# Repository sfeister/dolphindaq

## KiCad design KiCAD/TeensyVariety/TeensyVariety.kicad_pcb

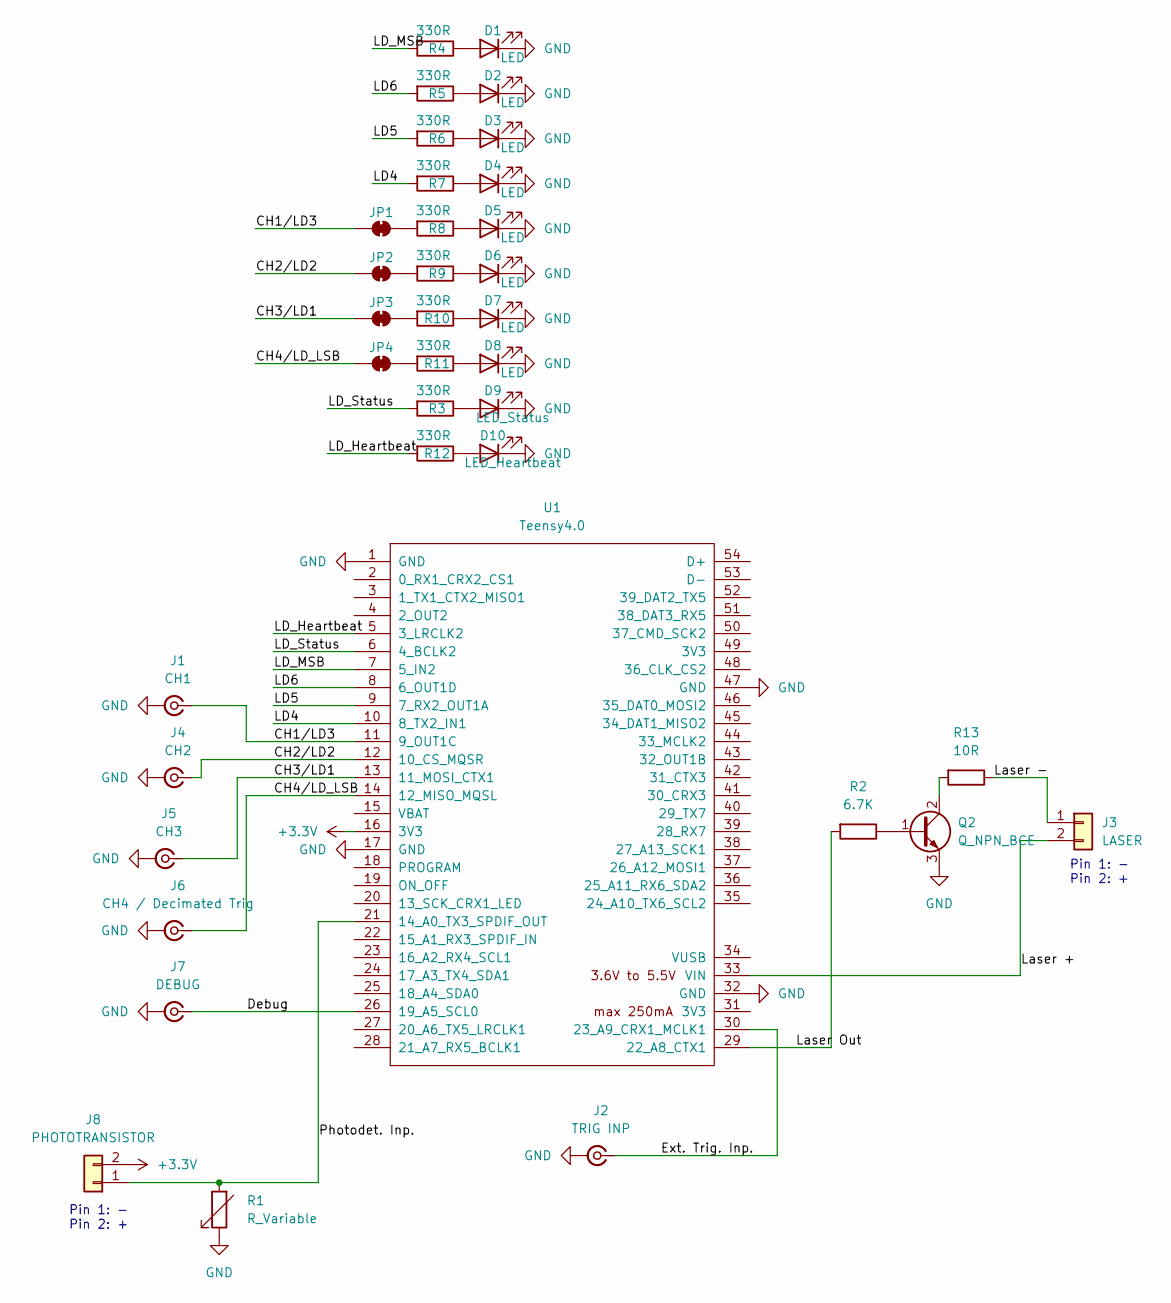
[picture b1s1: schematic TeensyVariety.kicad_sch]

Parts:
D1, D2, D3, D4, D5, D6, D7, D8: LED; LED_0805_2012Metric
D9: LED_Status; LED_0805_2012Metric
D10: LED_Heartbeat; LED_0805_2012Metric
J1: CH1; SMA_Amphenol_132134_Vertical
J2: TRIG INP; SMA_Amphenol_132134_Vertical
J3: LASER; JST_EH_S2B-EH_1x02_P2.50mm_Horizontal
J4: CH2; SMA_Amphenol_132134_Vertical
J5: CH3; SMA_Amphenol_132134_Vertical
J6: CH4 / Decimated Trig; SMA_Amphenol_132134_Vertical
J7: DEBUG; SMA_Amphenol_132134_Vertical
J8: PHOTOTRANSISTOR; JST_EH_S2B-EH_1x02_P2.50mm_Horizontal
JP1, JP2, JP3, JP4: Isolator; SolderJumper-2_P1.3mm_Bridged2Bar_Pad1.0x1.5mm
Q2: Q_NPN_BCE; SOT-23
R1: R_Variable; R_0805_2012Metric
R2: 6.7K; R_0805_2012Metric
R3, R4, R5, R6, R7, R8, R9, R10, R11, R12: 330R; R_0805_2012Metric
R13: 10R; R_0805_2012Metric
U1: Teensy4.0; Teensy40

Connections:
+3.3V: J8.2, U1.16 (3V3)
/CH1/LD3: J1.1 (In), JP1.1 (A), U1.11 (9_OUT1C)
/CH2/LD2: J4.1 (In), JP2.1 (A), U1.12 (10_CS_MQSR)
/CH3/LD1: J5.1 (In), JP3.1 (A), U1.13 (11_MOSI_CTX1)
/CH4/LD_LSB: J6.1 (In), JP4.1 (A), U1.14 (12_MISO_MQSL)
/Debug: J7.1 (In), U1.26 (19_A5_SCL0)
/Ext. Trig. Inp.: J2.1 (In), U1.30 (23_A9_CRX1_MCLK1)
/LD4: R7.2, U1.10 (8_TX2_IN1)
/LD5: R6.2, U1.9 (7_RX2_OUT1A)
/LD6: R5.2, U1.8 (6_OUT1D)
/LD_Heartbeat: R12.2, U1.5 (3_LRCLK2)
/LD_MSB: R4.2, U1.7 (5_IN2)
/LD_Status: R3.2, U1.6 (4_BCLK2)
/Laser +: J3.2, U1.33 (VIN)
/Laser -: J3.1, R13.1
/Laser Out: R2.2, U1.29 (22_A8_CTX1)
/Photodet. Inp.: J8.1, R1.2, U1.21 (14_A0_TX3_SPDIF_OUT)
GND: D1.1 (K), D2.1 (K), D3.1 (K), D4.1 (K), D5.1 (K), D6.1 (K), D7.1 (K), D8.1 (K), D9.1 (K), D10.1 (K), J1.2 (Ext), J2.2 (Ext), J4.2 (Ext), J5.2 (Ext), J6.2 (Ext), J7.2 (Ext), Q2.3 (E), R1.1, U1.1 (GND), U1.17 (GND), U1.32 (GND), U1.47 (GND)
unnamed: D1.2 (A), R4.1
unnamed: D2.2 (A), R5.1
unnamed: D3.2 (A), R6.1
unnamed: D4.2 (A), R7.1
unnamed: D5.2 (A), R8.1
unnamed: D6.2 (A), R9.1
unnamed: D7.2 (A), R10.1
unnamed: D8.2 (A), R11.1
unnamed: D9.2 (A), R3.1
unnamed: D10.2 (A), R12.1
unnamed: JP1.2 (B), R8.2
unnamed: JP2.2 (B), R9.2
unnamed: JP3.2 (B), R10.2
unnamed: JP4.2 (B), R11.2
unnamed: Q2.1 (B), R2.1
unnamed: Q2.2 (C), R13.2

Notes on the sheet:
Pin 1: - Pin 2: +

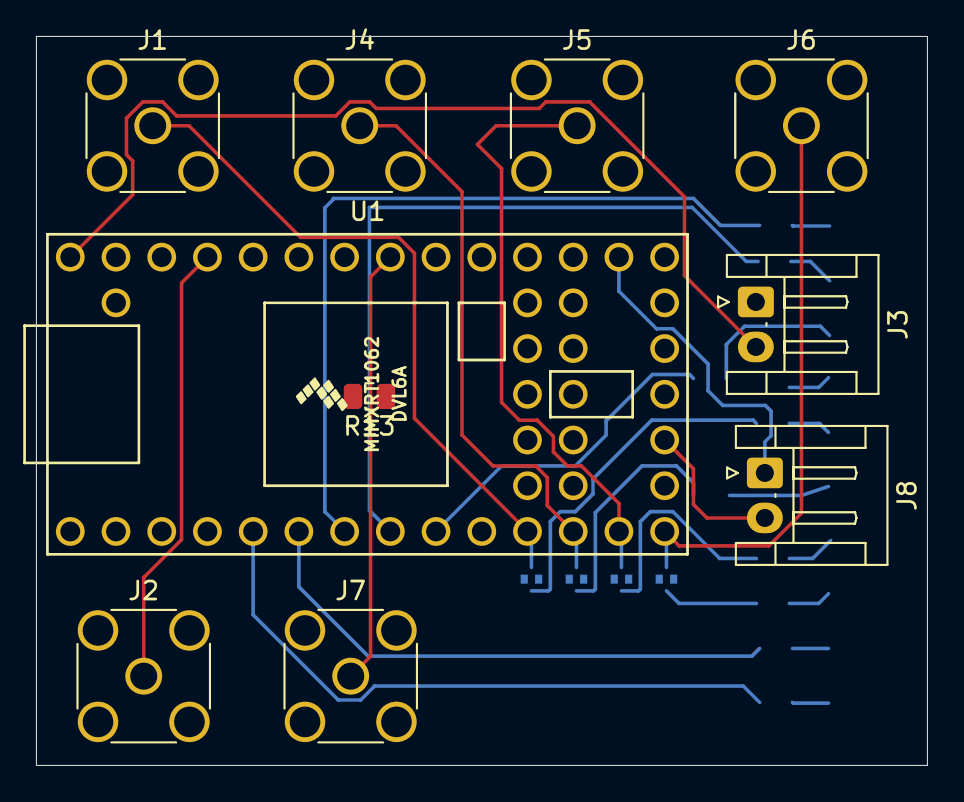
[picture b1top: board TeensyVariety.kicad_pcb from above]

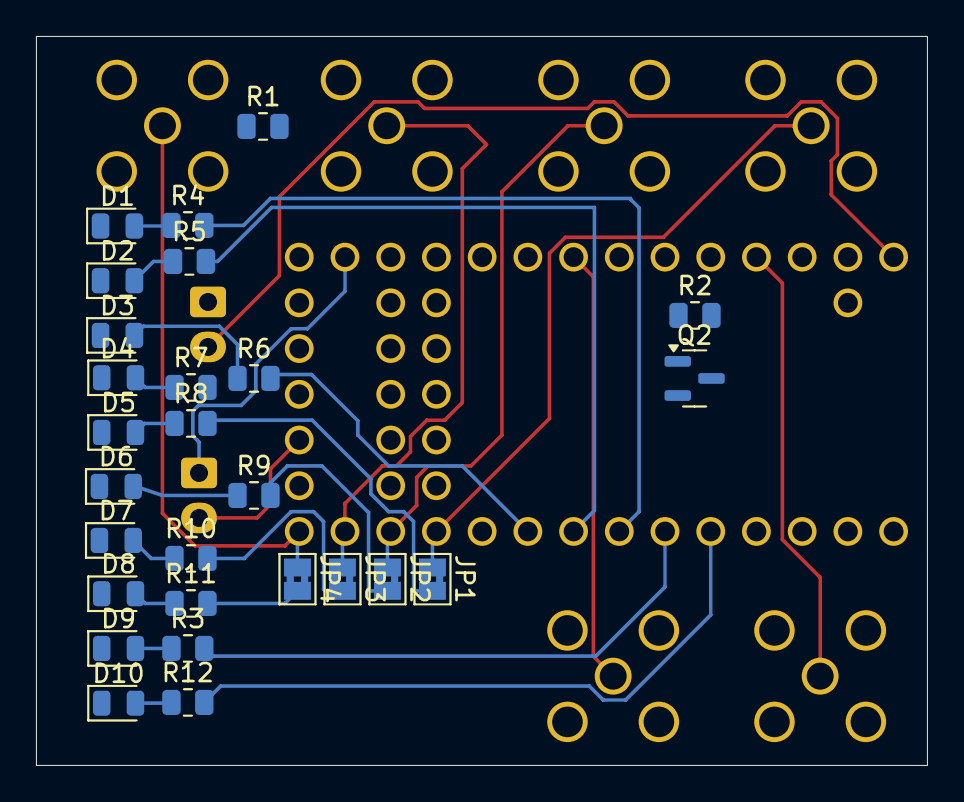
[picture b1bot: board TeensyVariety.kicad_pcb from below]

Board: 2 copper layers, 49.5 x 40.5 mm, 37 parts (27 on the bottom side), 34 nets.

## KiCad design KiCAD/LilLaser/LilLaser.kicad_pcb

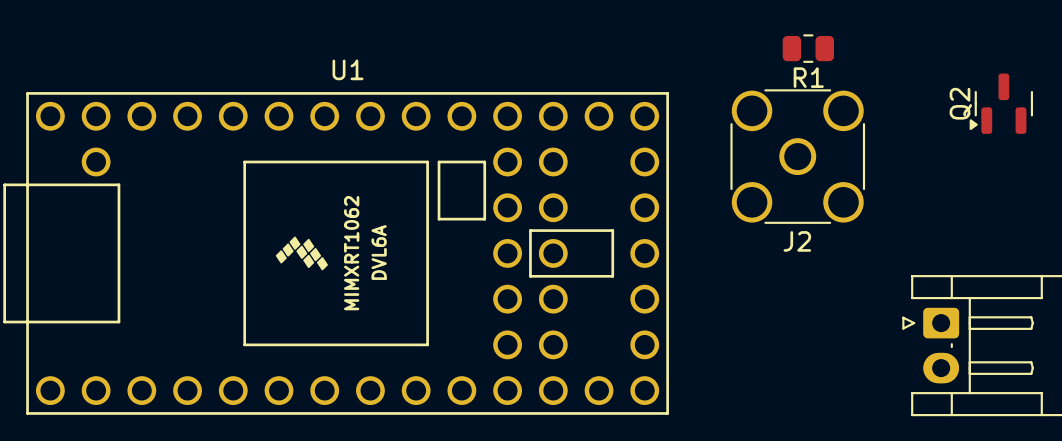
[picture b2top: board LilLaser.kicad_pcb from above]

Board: 2 copper layers, 5 parts (0 on the bottom side), 6 nets, no tracks yet.

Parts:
J2: Conn_Coaxial_Small; SMA_Amphenol_132134_Vertical
J3: Conn_01x02; JST_EH_S2B-EH_1x02_P2.50mm_Horizontal
Q2: Q_NPN_BCE; SOT-23
R1: R; R_0805_2012Metric
U1: Teensy4.0; Teensy40

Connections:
/Ext Trig Inp: J2.1 (In), U1.23 (16_A2_RX4_SCL1)
/Laser +: J3.2, U1.33 (VIN)
/Laser -: J3.1, Q2.2 (C)
/Laser Out: R1.2, U1.22 (15_A1_RX3_SPDIF_IN)
GND: J2.2 (Ext), Q2.3 (E), U1.1 (GND), U1.17 (GND), U1.32 (GND)
unnamed: Q2.1 (B), R1.1

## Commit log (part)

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2021-01-23 Adding Protobuffer templates
2021-01-23 Updated protobuffers
2021-01-23 Updated protobuf folders
2021-01-27 Working on diode_h5 to store the diode type to HDF5 files
2021-01-28 test7-data-server.py and test7-diode1-client.py are working great together! Now just need to have the server keep on looking for connections, and have the clients handle a failure of the server
2021-02-08 Continuing work on data-server; switching over to work on protobuf-c code for Matsunet
2022-06-08 Old update to makefile, not inspected
2022-06-08 Added simple.proto example as directly copied from NanoPB examples folder
2022-06-09 Including NanoPB header files and source code files for convenience
2022-06-09 Added scoping to the diode protobuffer specification, such that Data and Trace don't conflict with other scopes
2022-06-09 New clients in Python to match up with the Nucleo codes
2022-06-09 net10 client now receives hello, settings, and a single trace
2022-06-10 Net10 breaks on the microcontroller side after sending 100 to 500 commits.
2022-06-20 Client for the ADC network test, net12
2022-06-23 Updated terminology of the traces and settings for the photodiode signal
2022-07-01 Net14 client is working well; ready for a test on ADC data
2022-07-06 Added various additional low-level settings from the H7 firmware
2022-07-06 Fixed bug with seconds being represented as uint32 instead of double
2022-07-06 Upgraded from proto2 to proto3 syntax to include the Well-known 'Timestamp' type from Google, so that I can timestamp shots
2022-07-06 Reverted to proto2 because it includes a 'has_' syntax for singletons that I find useful in distinguishing between values of zero, and default values'
2022-07-06 Including protobuf source code for Timestamp well known type
2022-07-11 Updated protobuf for diode to indicate higher level dt - at the ADC conversion level, rather than just the returned trace
2022-07-11 Removed dt_secs option from protobuf for consistency, just using dt and inferred seconds
2022-07-12 Updated name of shot_time from the plural version, to be more consistent
2022-07-12 Continuing to add optional metrics fields
2022-07-13 Added metrics batch size to settings
2022-07-13 Fixed metrics batch size to be an integer
2022-07-14 Added LabVIEW SCPI-style drivers for the Diode H7 20220713 firmware
2022-07-14 Added a new Python folder to hold scripts such as those for data recording onto the Beaglebone
2022-07-15 Added SCPI set/get of trace decimation to the LabVIEW SCPI-like driver
2022-07-15 Test8 server demonstrated 60k acquisition batches for several minutes saved to HDF5, capturing vast majority of shots metrics
2022-07-15 Minor adjustments to gitignores
2022-07-18 Adding optional, simpler arrays for timestamps within metrics
2022-07-19 Added an alternate, precision timing source in the metrics
2022-07-19 Updated naming of the alternative precision timer
2022-07-19 Added a LabVIEW example of visualizing result from HDF5
2022-07-20 LabVIEW portion of this commit goes along with Nucleo Diode H7 20220719 firmware
2022-07-20 Updating linecam protocol file as I develop Hamamatsu line camera H7 firmware
2022-07-23 Displays for the Hamaline camera
2022-07-24 Adding a new device: Rosie
2022-07-29 Updated all code to match Nucleo firmware 20220728 - note addition of metadata to the diode-recorder
2022-08-01 Updating VIs to call common subroutines
2022-08-03 Updated linecam proto file to include the T1 delay time
2022-08-03 Updating diode controls
2022-09-01 Updating lab launcher and tested; it basically works - Rosie and Diode control panels are now ready to go back into real testing in a lab setting, including saving to local file
2023-01-18 Lingering change to LabVIEW aliases from months ago
2023-02-15 Updated Rosie SCPI keywords to match Nucleo Rosie 20230215 firmware
2023-02-27 Beginning EPICS driver for Rosie firmware; confirmed that this first simplest StreamDevice startup script works for getting SCPI identification
2023-02-27 Adding Rosie into EPICS works well; created example Python code of how to translate between global trigger count and local trigger count for a rosie device
2023-03-03 Created a new device, BlinkSync, which helps with camera synchronization by providing a visual display of a trigger count
2023-04-04 Updating Serial BlinkSync to work with a frequency option
2023-04-05 Unfinished pulse generator; new fake espec
2023-04-05 Added a fake electron spectrometer
2023-04-17 Untested Teensy pulse generator source code is ready to go, along with EPICS controller
2023-04-17 Updated firmware label for Teensy Pulsegen
2023-04-17 Added timeout for Serial search for Teensy board, so it will power on even when no serial devices are present
2023-04-17 Untested port of ROSIE to Teensy, without several of the features
2023-04-17 Set default decimation on Teensy ROSIE to 100, to match other
2023-04-17 Added option to enable or disable output for Teensy pulse generator
2023-04-18 Pulse generator for Teensy 3.2 is tested and working, added comment about working to 1 kHz
2023-04-18 Tested on workbench; Teensy ROSIE and Teensy PulseGen both seem to be working as written
2023-04-19 Added removal of mouse cursor for auto-boot display
2023-04-19 FauxSpec is now tested and the trigger count can be remotely updated through EPICS
2023-04-19 slight updates to way I am writing about Rosie, nothing substantial
2023-04-19 Updating TeensyPulse database to include ability to enable and disable trigger outputs
2023-04-19 Updated software timers for pulse generator to be 64-bit so we can have long delay times, like up to minutes
2023-04-19 Added occasional scanning of the identification for the device, since otherwise it's not showing up as anything
2023-04-19 Adding fauxspec analysis script
2023-06-14 Lengthened default pulse width of pulse generator Teensy to 100 microseconds for compatibility with Mightex cameras
2023-09-24 Created setup for a laser-style pulse profile
2023-10-12 Updated for DDAQ workshop demo - Photodiode now compiles (barely, with hacks on my own PC libraries for relative paths etc due to protobufs
2023-10-12 Continuing work and have created diode for teensy
2023-11-04 Found a typo in initial time delays, probably no impact, but fixed for PulseGeneratorSerial Teensy
2023-11-06 Demo for DDW
2023-11-06 Updated the TeensyDiode to work well, tested and ready for next stages
2023-11-06 Brought in the Phoebus / CS-Studio file for controlling the sidekick version 3 with pen lasers. Still needs some improvement
2023-12-24 Adding a design for a laser-cut box to hold ROSIE device
2024-03-22 Updating the sidekick elements
2024-03-22 Adding some generic PC monitor CA servers and clients
2024-03-25 Adding a very simple pulse counter with EPICS streamdevice tie-in
2024-03-28 Added a clock server and also added a timing control demo
2024-03-28 Continuing to improve the pc info server
2024-03-30 Working streamdevice for Nucleo-H7 Diode with 20240330 firmware
2024-03-30 Updated protobufs to allow for a fifth-from-maximum peak metric
2024-03-30 Added compiled protobufs to the repo
2024-03-31 Ready for experiments I believe - most all the main ones are installed
2024-04-06 Getting the sidekick v3 system working
2024-04-09 Adding control panel for Sidekick v3
2024-04-15 Working untested laser pulse profile version
2024-04-15 Major changes including increasing SCPI input buffer in LilLaser firmware to allow for sending a large 1D array - epics is tested with LilLaser and is working
2024-04-18 Adding EPICS variables for 1D array versions of firmware
2024-05-01 Adding the proto library for Arduino
2024-05-02 Flipped polarity on the phototransistor elements and noted these changes -- all required only for Model 4 due to its flipped electronic polarity for the phototransistors
2024-05-02 Added two more debugging firmwares
2024-05-02 Added more troubleshooting firmwares
2024-05-02 Yet more troubleshooting firmware
2024-05-02 A simple blinker
2024-05-03 Starting to work on firmwares with variable PWM frequencies for moving to deal with digital detectors
2024-05-03 Trying to get the analogwritefrequency to actually work
2024-05-03 Lowing PWM rates to 10 kHz to allow all those signals to transmit digitally rather than trying to smooth the signals in an analog way
2024-05-03 Slowed down the targetdebugger analogread and put it on the ADC module
2024-05-03 Added two milliseconds of averaging to smooth out trace
2024-07-25 Designing some boxes for Rosie - the Tiny one works great
2024-07-25 Successful implementation of PVA server for photodiode
2024-07-25 Attempting to cleverly smooth the PWM signal by matching the ADC sampling time on the diode (2.20 microseconds as configured) to the PWM period time on the laser (2.20 microseconds as configured) -- 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
2024-07-26 Fixed the Diode drift problem by letting the ADC free run conversions in the background and only activate DMA at trigger
2024-07-26 Ran down a nasty issue in the Teensy4 ADC-DMA setup of how to call my own interrupt; got it working. This all solved the issue (I hope) that was perhaps due to the millisecond timer and waiting a who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
2024-07-26 Adding a script to start the Teensy USB data server
2024-07-27 Updated diagram for color scheme and more
2024-08-02 Exploring normative types
2024-08-02 Adding in uniqueId and settings attributes to the PVA Server
2024-08-09 Setting up for demo of sidekick v3 high-rep-rate; all systems working
2024-08-22 UI changes
2024-08-23 Updated UI and also minor edits to unfinished PCB
2024-08-28 Working setup for bookshelf sidekick
2024-08-28 Updated all Teensy sidekick external interrupts to have highest priority to avoid dropping triggers; slight updates to UI to ensure trigger synchronization
2024-08-28 Added caget, caput, pvget, and pvput to make life easier
2025-05-03 lingering changes from sidekick HRR
2025-05-03 Adding a TFT protobuf for simple data transfer to/from a TFT display node
2025-05-03 Fixed workflow for Arduino nanopb library ddaqproto
2025-05-03 TFT not quite working but close
2025-05-04 Working at 1 Hz for Waveshare TFTSerial device
2025-05-22 Bugfixes to TargetTFTSerial
2025-05-22 Continued improvements to TargetTFT for PROBIES
2025-06-06 Adding CAMPROBIES and working towards sidekick v5
2025-06-07 Adding the variables for the TFTPROBIES
2025-06-16 Updated Teensy TFT to allow for variable time delay between trigger arrival and TFT display, as well as enabling better data flow
2025-06-16 Added an additional delay for the blanking of the screen
2025-06-16 Updating delay time to reflect the 80 milliseconds built into the new TFT firmware. Finding that about 80 milliseconds + 50 milliseconds is ideal, or 130 milliseconds camera delay
2025-06-16 Adding a few PVs to the CS-studio control panels
2025-06-19 Beginning (but not created yet) a PVA server for the PROBIES image input
2026-02-03 Added various CAD files for the Sidekick Model 3 Bookshelf Form-Factor
2026-06-12 Adding in some scripts I had on the Beaglebone Black
2026-06-12 Adding in more helper scripts I had on the Beaglebone Black
2026-06-16 Adding CAMPROBIES variables
2026-06-16 Adding a wrapper for 'watch' of the manage-iocs log files
2026-06-16 Removed TFT differential draw for PROBIES, and clipped data to a known range in TFTPROBIES-SIM. The second change is to reduce the drawing of yellow regions when infer_probies() returns a slightly ne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
2026-06-17 Added a trigger count to bottom right of PROBIES image as well - so we can verify image integrity by looking at all sides of the image
2026-06-17 Dropped the trace more properly by unlocking trace and removing ripe_trace flags
2026-06-17 Undid the last change as I see encode_trace already did this
2026-06-17 Testing the synchronous control with current system
2026-06-18 First efforts at Bluesky integration
2026-06-18 Explorations in ophyd-async and ELECTRON-DAQ data source
2026-06-22 Exploring grouping CA channels into Devices for Bluesky
2026-06-23 Working towards Bluesky run plans for changing laser powers and then saving to disk
2026-06-23 Bringing in Tiled server to Bluesky
